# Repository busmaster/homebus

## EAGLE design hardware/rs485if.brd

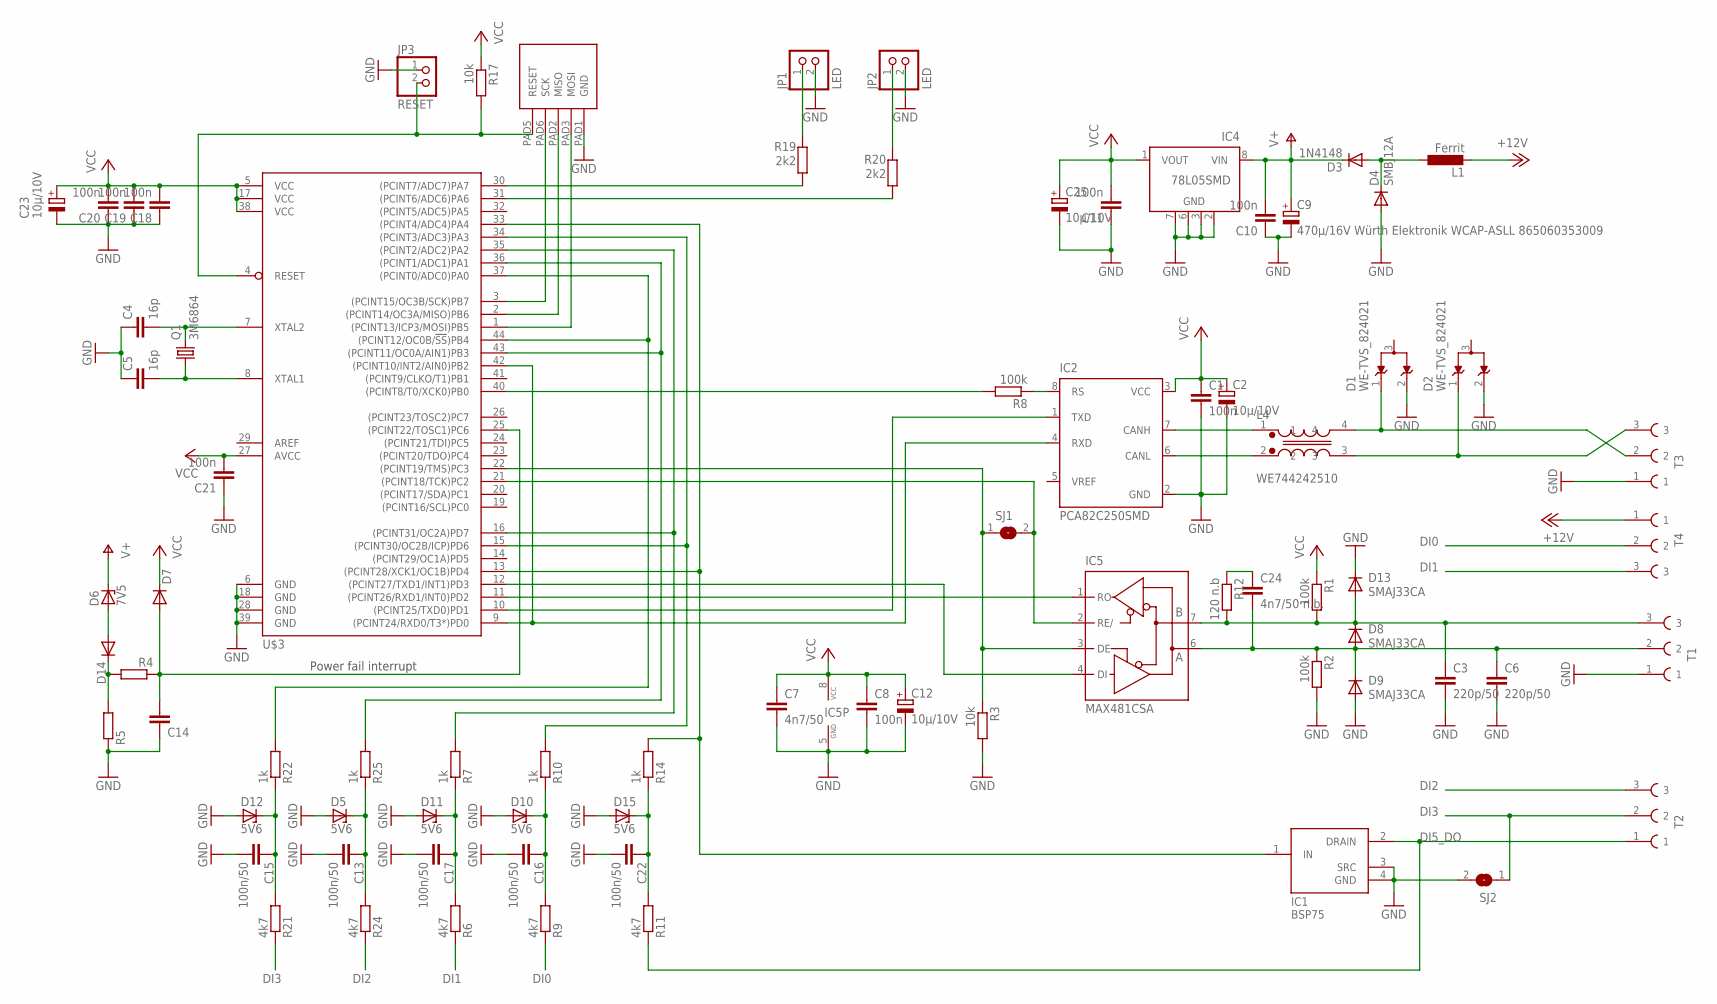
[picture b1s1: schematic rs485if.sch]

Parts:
C1, C8, C10, C11, C18, C19, C20, C21: 100n; C0603
C2, C12, C23, C25: 10µ/10V; A/3216-18W
C3, C6: 220p/50; C0603
C4, C5: 16p; C0603
C7: 4n7/50; C0603
C9: 470µ/16V Würth Elektronik WCAP-ASLL 865060353009; SANYO-OSCON_SMD_E7
C13, C15, C16, C17, C22: 100n/50; C0603
C14: C-EUC0603; C0603
C24: 4n7/50 n.b.; C0603
D1, D2: WE-TVS_824021; WE-TVS_SOT23-3L
D3: 1N4148; SOD80C
D4: SMBJ12A; SMB
D5, D10, D11, D12, D15: 5V6; SOD80C
D6: 7V5; SOD80C
D7, D14: DIODE-SOD80C; SOD80C
D8, D9, D13: SMAJ33CA; DO214AC
IC1: BSP75; SOT223
IC2: PCA82C250SMD; SO8
IC4: 78L05SMD; SO08
IC5: MAX481CSA; SO08
JP1, JP2: LED; 1X02
JP3: RESET; 1X02
L1: Ferrit; L1806
L4: WE744242510; WE-SLM
Q1: 3M6864; SM49
R1, R2, R8: 100k; R0603
R3, R17: 10k; R0603
R4, R5: R-EU_R0603; R0603
R6, R9, R11, R21, R24: 4k7; R0603
R7, R10, R14, R22, R25: 1k; R0603
R12: 120 n.b; R0603
R19, R20: 2k2; R0603
SJ1, SJ2: SJ
T1, T2: MKDSO_2.5/3_R; PHOENIX_MKDSO_2.5/3_R
T3, T4: MKDSO_2.5/3_L; PHOENIX_MKDSO_2.5/3_L
U$1: ATMEL_ISP
U$3: ATMEGA644; TQFP44

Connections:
#RESET: JP3.2, R17.2, U$1.PAD5 (RESET), U$3.4 (RESET)
+12V: L1.2, T4.1
A: C6.1, C24.2, D8.A, D9.C, IC5.6 (A), R2.1, T1.2
B: C3.1, D8.C, D13.A, IC5.7 (B), R1.2, R12.2, T1.3
B+: D1.1, L4.4, T3.2
B-: D2.1, L4.3, T3.3
DI0: R9.1, T4.2
DI1: R6.1, T4.3
DI2: R24.1, T2.3
DI3: R21.1, SJ2.1, T2.2
DI5_DO: IC1.2 (DRAIN), R11.1, T2.1
GND: C1.2, C2.-, C3.2, C4.1, C5.1, C6.2, C7.2, C8.2, C9.-, C10.1, C11.1, C12.-, C13.2, C14.1, C15.2, C16.2, C17.2, C18.1, C19.1, C20.1, C21.1, C22.2, C23.-, C25.-, D1.2, D2.2, D4.A, D5.A, D9.A, D10.A, D11.A, D12.A, D13.C, D15.A, IC1.3 (SRC), IC1.4 (GND), IC2.2 (GND), IC4.2 (GND), IC4.3 (GND), IC4.6 (GND), IC4.7 (GND), IC5.5 (GND), JP1.2, JP2.2, JP3.1, R2.2, R3.2, R5.1, SJ2.2, T1.1, T3.1, U$1.PAD1 (GND), U$3.6 (GND), U$3.18 (GND), U$3.28 (GND), U$3.39 (GND)
unnamed: R8.2, U$3.40 ((PCINT8/T0/XCK0)PB0)
unnamed: C24.1, R12.1
unnamed: IC2.1 (TXD), U$3.10 ((PCINT25/TXD0)PD1)
unnamed: U$1.PAD3 (MOSI), U$3.1 ((PCINT13/ICP3/MOSI)PB5)
unnamed: U$1.PAD2 (MISO), U$3.2 ((PCINT14/OC3A/MISO)PB6)
unnamed: U$1.PAD6 (SCK), U$3.3 ((PCINT15/OC3B/SCK)PB7)
unnamed: IC1.1 (IN), R14.2, U$3.13 ((PCINT28/XCK1/OC1B)PD4), U$3.33 ((PCINT4/ADC4)PA4)
unnamed: C13.1, D5.C, R24.2, R25.1
unnamed: IC2.7 (CANH), L4.1
unnamed: IC5.4 (DI), U$3.12 ((PCINT27/TXD1/INT1)PD3)
unnamed: IC2.4 (RXD), U$3.9 ((PCINT24/RXD0/T3*)PD0), U$3.42 ((PCINT10/INT2/AIN0)PB2)
unnamed: IC5.1 (RO), U$3.11 ((PCINT26/RXD1/INT0)PD2)
unnamed: IC5.3 (DE), R3.1, SJ1.1, U$3.22 ((PCINT19/TMS)PC3)
unnamed: C4.2, Q1.2, U$3.7 (XTAL2)
unnamed: C5.2, Q1.1, U$3.8 (XTAL1)
unnamed: IC2.6 (CANL), L4.2
unnamed: C15.1, D12.C, R21.2, R22.1
unnamed: C16.1, D10.C, R9.2, R10.1
unnamed: D3.A, D4.C, L1.1
unnamed: C17.1, D11.C, R6.2, R7.1
unnamed: D6.A, D14.A
unnamed: JP2.1, R20.1
unnamed: R19.2, U$3.30 ((PCINT7/ADC7)PA7)
unnamed: R20.2, U$3.31 ((PCINT6/ADC6)PA6)
unnamed: IC5.2 (RE/), SJ1.2, U$3.21 ((PCINT18/TCK)PC2)
unnamed: IC2.8 (RS), R8.1
unnamed: D14.C, R4.2, R5.2
unnamed: C22.1, D15.C, R11.2, R14.1
unnamed: R10.2, U$3.15 ((PCINT30/OC2B/ICP)PD6), U$3.34 ((PCINT3/ADC3)PA3)
unnamed: R7.2, U$3.16 ((PCINT31/OC2A)PD7), U$3.35 ((PCINT2/ADC2)PA2)
unnamed: R25.2, U$3.36 ((PCINT1/ADC1)PA1), U$3.43 ((PCINT11/OC0A/AIN1)PB3)
unnamed: R22.2, U$3.37 ((PCINT0/ADC0)PA0), U$3.44 ((PCINT12/OC0B/!SS!)PB4)
unnamed: JP1.1, R19.1
unnamed: C14.2, D7.A, R4.1, U$3.25 ((PCINT22/TOSC1)PC6)
V+: C9.+, C10.2, D3.C, D6.C, IC4.8 (VIN)
VCC: C1.1, C2.+, C7.1, C8.1, C11.2, C12.+, C18.2, C19.2, C20.2, C21.2, C23.+, C25.+, D7.C, IC2.3 (VCC), IC4.1 (VOUT), IC5.8 (VCC), R1.1, R17.1, U$3.5 (VCC), U$3.17 (VCC), U$3.27 (AVCC), U$3.38 (VCC)

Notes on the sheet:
Power fail interrupt

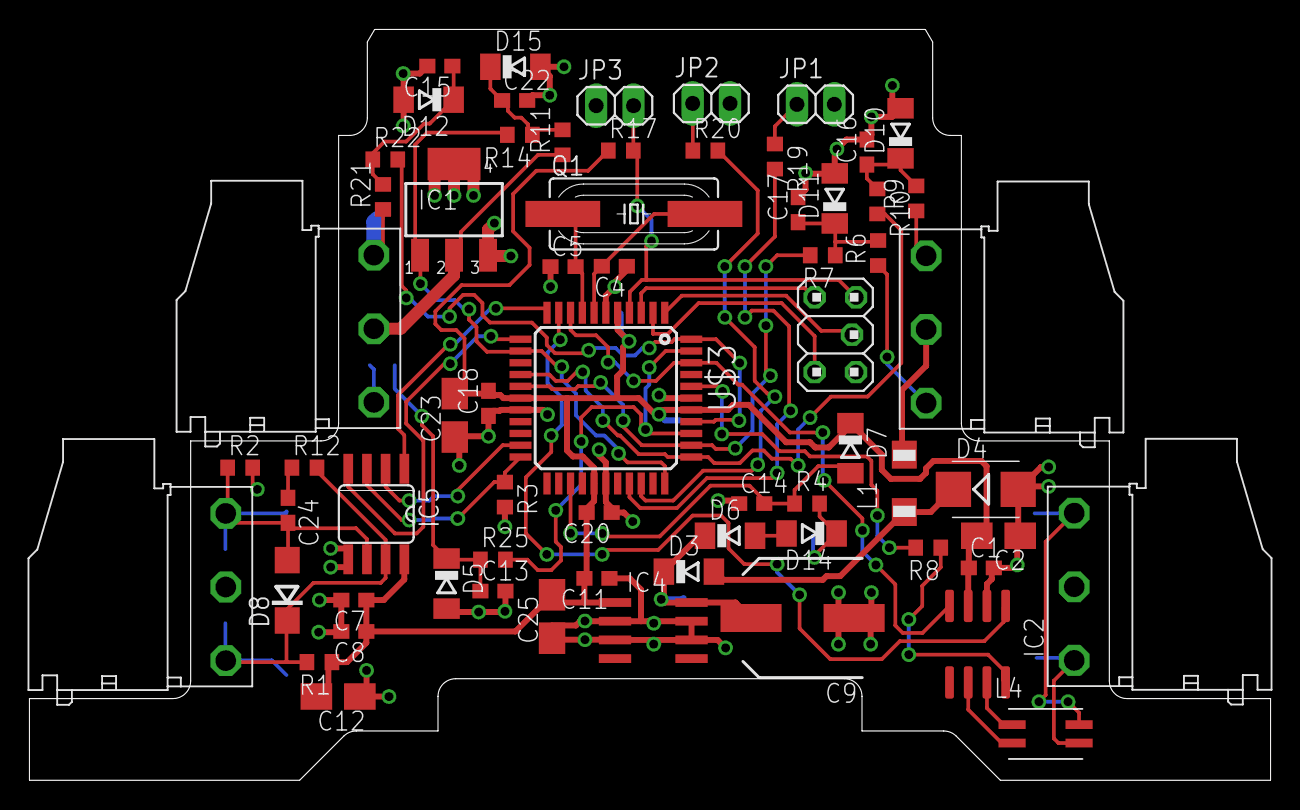
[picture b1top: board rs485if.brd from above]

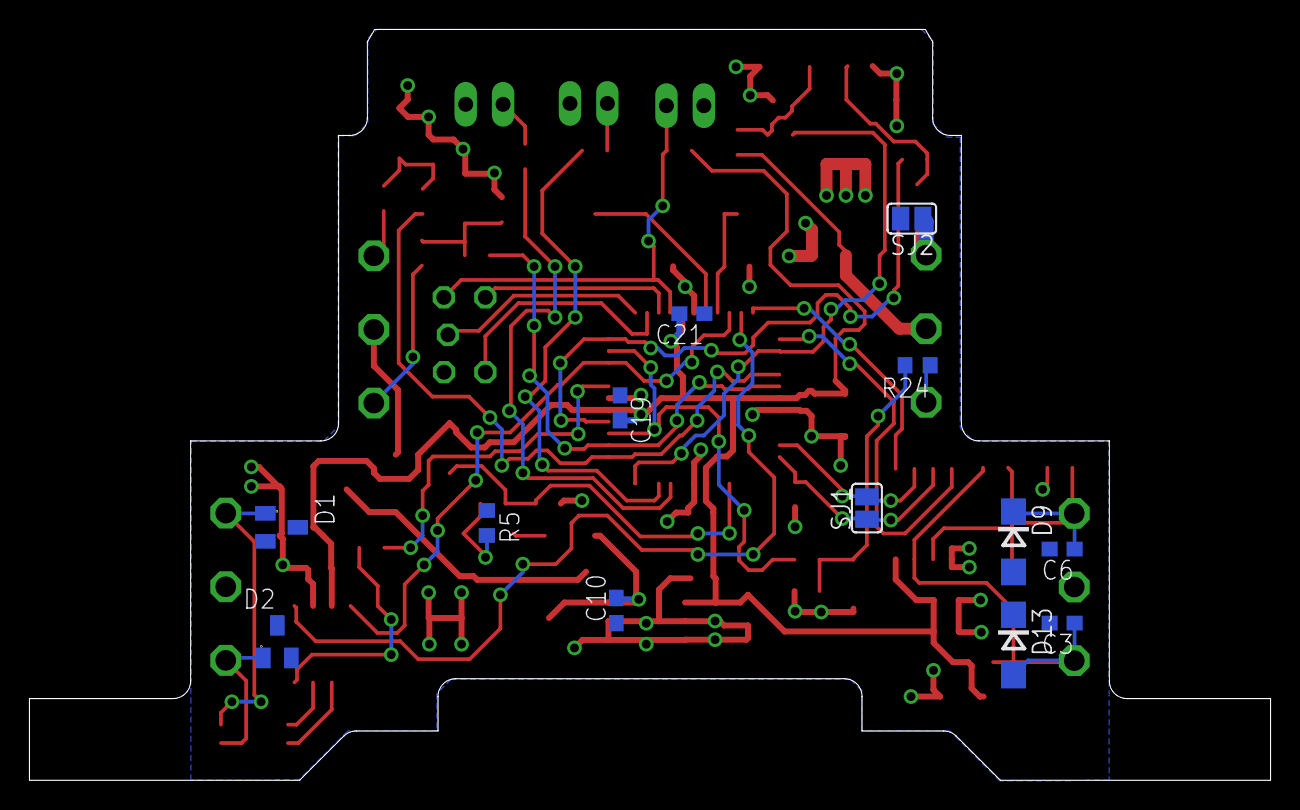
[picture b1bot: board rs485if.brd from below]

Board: 2 copper layers, 84.3 x 51.0 mm, 79 parts (13 on the bottom side), 48 nets.

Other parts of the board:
U$4: GEHÄUSE_PHOENIX_BC_17.8

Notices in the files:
parts and their libraries:
EagleLibrary_Wuerth_Elektronik_eiSos_V6_: Copyright: Würth Elektronik
